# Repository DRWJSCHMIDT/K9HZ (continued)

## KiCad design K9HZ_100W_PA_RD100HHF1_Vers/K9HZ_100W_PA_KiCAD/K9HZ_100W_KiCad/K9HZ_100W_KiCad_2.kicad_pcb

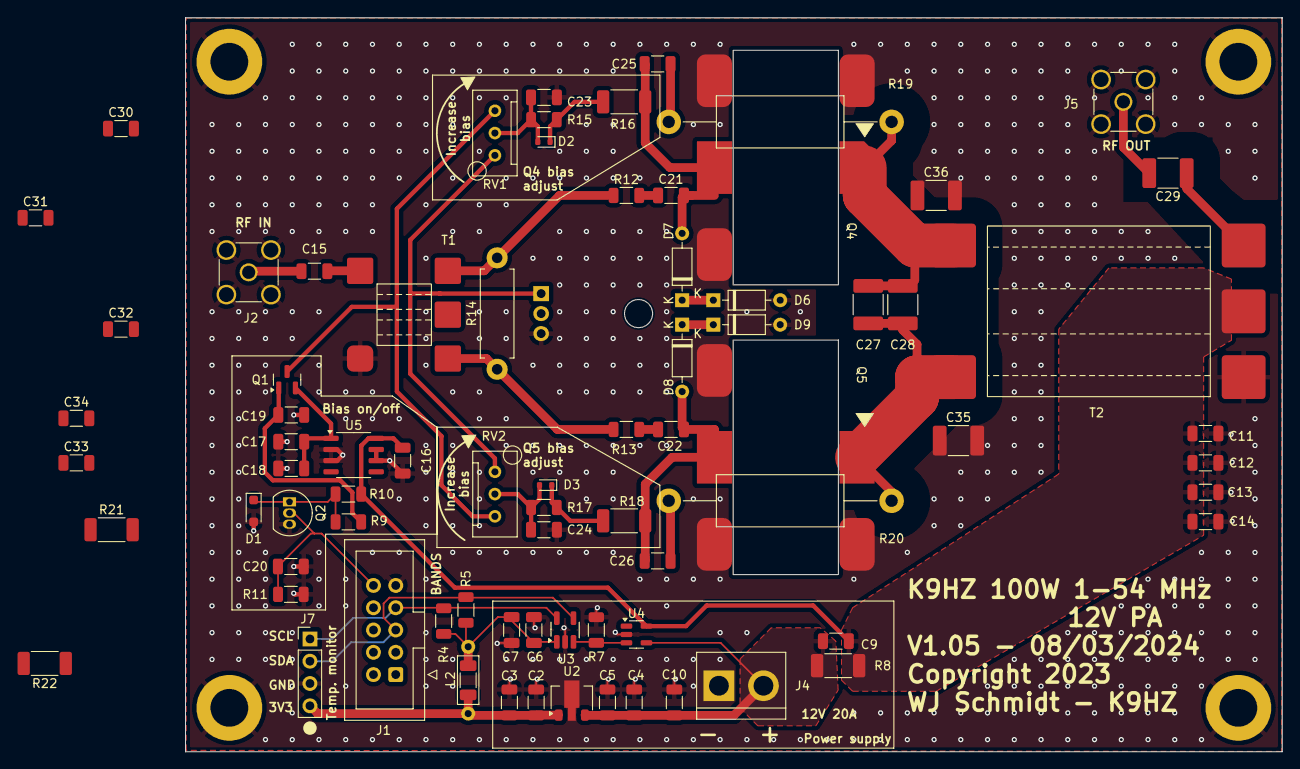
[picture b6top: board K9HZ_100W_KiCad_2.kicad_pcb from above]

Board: 2 copper layers, 125.0 x 83.7 mm, 83 parts (1 on the bottom side), 35 nets.

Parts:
C2, C4, C7, C9, C10, C15, C18, C20, C23, C24, C30, C31: 0.1uF 50V; C_1206_3216Metric
C3: 2.2uF 6V; C_1206_3216Metric
C5: 1uF 16V; C_1206_3216Metric
C6: 10uF 6V; C_1206_3216Metric
C11, C12, C13, C14: 0.1uF; C_1206_3216Metric
C16, C17: 1uF 50V; C_1206_3216Metric
C19, C21, C22: 0.01uF 50V; C_1206_3216Metric
C25, C26: 4.7nF 100V; C_1206_3216Metric
C27, C28: 470pF 500V; C_1812_4532Metric_Pad1.57x3.40mm_HandSolder
C29: 0.1uF 500V; C_1812_4532Metric_Pad1.57x3.40mm_HandSolder
C32, C33: 100 pF 50V; C_1206_3216Metric
C34: 200pF 50V; C_1206_3216Metric
C35, C36: 100pF 500V; C_1812_4532Metric_Pad1.57x3.40mm_HandSolder
D1: 7.1V 1W; D_SOD-323_HandSoldering
D2, D3: 1N4148; D_SOD-523
D6, D7, D8, D9: 3.6V; D_DO-35_SOD27_P7.62mm_Horizontal
H1, H2, H3, H4: MountingHole_4.3mm_M4_DIN965_Pad
J1: BANDS; IDC-Header_2x05_P2.54mm_Vertical
J2: RF_IN; SMA_Amphenol_901-144_Vertical
J4: 12V, 20A; TerminalBlock_bornier-2_P5.08mm
J5: RF_OUT; SMA_Amphenol_901-144_Vertical
J7: Temp monitor; PinHeader_1x04_P2.54mm_Vertical
L2: FB; L_Axial_L5.3mm_D2.2mm_P7.62mm_Horizontal_Vishay_IM-1
L3: FB; L_1206_3216Metric_Pad1.22x1.90mm_HandSolder
Q1: BSS84; SOT-23
Q2: BS170; TO-92_Inline
Q3: BD677; TO-126-3_Horizontal_TabUp
Q4: RD100HHF1C; RD100HHF1-suspended
Q5: RD100HHF1C; RD100HHF1-suspended-v2
R4, R5: 5k6; R_1206_3216Metric
R7: 3.0k 1%; R_1206_3216Metric
R8: 0.005 Ohm 4W; R_2010_5025Metric_Pad1.40x2.65mm_HandSolder
R9: 3k; R_1206_3216Metric
R10: 510R; R_1206_3216Metric
R11: 6k8; R_1206_3216Metric
R12, R13: 10R; R_1206_3216Metric
R14: 200R 2W; R_Axial_DIN0411_L9.9mm_D3.6mm_P12.70mm_Horizontal
R15, R17: 220R; R_1206_3216Metric
R16, R18: 1k; R_2010_5025Metric_Pad1.40x2.65mm_HandSolder
R19, R20: 150R 3W; R_Axial_DIN0614_L14.3mm_D5.7mm_P25.40mm_Horizontal
R21, R22: 2.2k; R_2010_5025Metric_Pad1.40x2.65mm_HandSolder
RV1, RV2: 2.2k; Potentiometer_Bourns_3296W_Vertical
T1: BN43-2402; Toroid_6Pin_BN-43-2402_7mm_6.2mm
T2: BN43-3312; Toroid_6Pin_BN-43-3312_19.5mm_25.4mm
U2: AP7381-33Y-13; SOT-89-3
U3: MCP3021A0T-E/OT; SOT-23-5_HandSoldering
U4: ZXCT1010; SOT-23-5
U5: L4931CDT50; SO-8_3.9x4.9mm_P1.27mm

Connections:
+3V3: C2.2, C3.2, J7.4, L2.1, L3.1, U2.1 (VO)
+12P: C9.2, C11.1, C12.1, C13.1, C14.1, C16.2, R8.1, R10.1, T2.4 (SC), U4.5 (Vs-), U5.8 (VI)
+12V: C4.2, C5.2, C9.1, C10.1, J4.2, R8.2, U2.3 (VI), U4.4 (Vs+)
/RXTX: C20.2, J1.10, Q2.2 (G), R11.2
/SCL: J1.7, J7.1, R4.2, U3.5 (SCL)
/SDA: J1.5, J7.2, R5.2, U3.4 (SDA)
GND: C2.1, C3.1, C4.1, C5.1, C6.1, C7.1, C10.2, C11.2, C12.2, C13.2, C14.2, C16.1, C17.1, C18.1, C19.1, C20.1, C23.2, C24.1, C32.1, C33.1, C35.2, C36.2, D1.2 (A), D6.2 (A), D9.2 (A), H1.1, H2.1, H3.1, H4.1, J1.9, J2.2 (Ext), J4.1, J5.2 (Ext), J7.3, Q2.3 (S), Q3.3 (E), Q4.2 (S), Q5.2 (S), R7.1, R11.1, T1.2 (AB), T2.1 (AA), U2.2 (GND), U3.2 (VSS), U4.2 (GND), U5.2 (GND), U5.3 (GND), U5.6 (GND), U5.7 (GND)
unnamed: C21.2, C30.2, R12.1
unnamed: C22.2, C31.2, R13.1
unnamed: C25.1, R19.2
unnamed: C26.1, R20.2
unnamed: D1.1 (K), Q2.1 (D), R9.1, R10.2
unnamed: C23.1, D2.2 (A), R15.1, RV1.2
unnamed: D2.1 (K), R15.2, R16.1
unnamed: C24.2, D3.2 (A), R17.1, RV2.2
unnamed: D3.1 (K), R17.2, R18.1
unnamed: D6.1 (K), D7.1 (K)
unnamed: C25.2, D7.2 (A), Q4.3 (G), R12.2, R13.2, R16.2, R21.2
unnamed: C26.2, D8.2 (A), Q5.3 (G), R18.2, R22.1
unnamed: D8.1 (K), D9.1 (K)
unnamed: C15.1, J2.1 (In)
unnamed: C29.2, J5.1 (In)
unnamed: Q1.3 (D), RV1.3, RV2.3
unnamed: C19.2, Q1.1 (G), R9.2
unnamed: C17.2, C18.2, Q1.2 (S), U5.1 (VO)
unnamed: Q3.1 (B), RV1.1, RV2.1
unnamed: C27.1, C28.1, C36.1, Q4.1 (D), R19.1, T2.3 (SA)
unnamed: C27.2, C28.2, C35.1, Q5.1 (D), R20.1, T2.5 (SB)
unnamed: R21.1, R22.2
unnamed: C15.2, T1.1 (AA)
unnamed: C22.1, C31.1, C32.2, C34.1, R14.1, T1.3 (SA)
unnamed: C21.1, C30.1, C33.2, C34.2, R14.2, T1.5 (SB)
unnamed: C29.1, T2.2 (AB)
unnamed: R7.2, U3.3 (AIN), U4.3 (OUT)
unnamed: C6.2, C7.2, L2.2, L3.2, R4.1, R5.1, U3.1 (VDD)

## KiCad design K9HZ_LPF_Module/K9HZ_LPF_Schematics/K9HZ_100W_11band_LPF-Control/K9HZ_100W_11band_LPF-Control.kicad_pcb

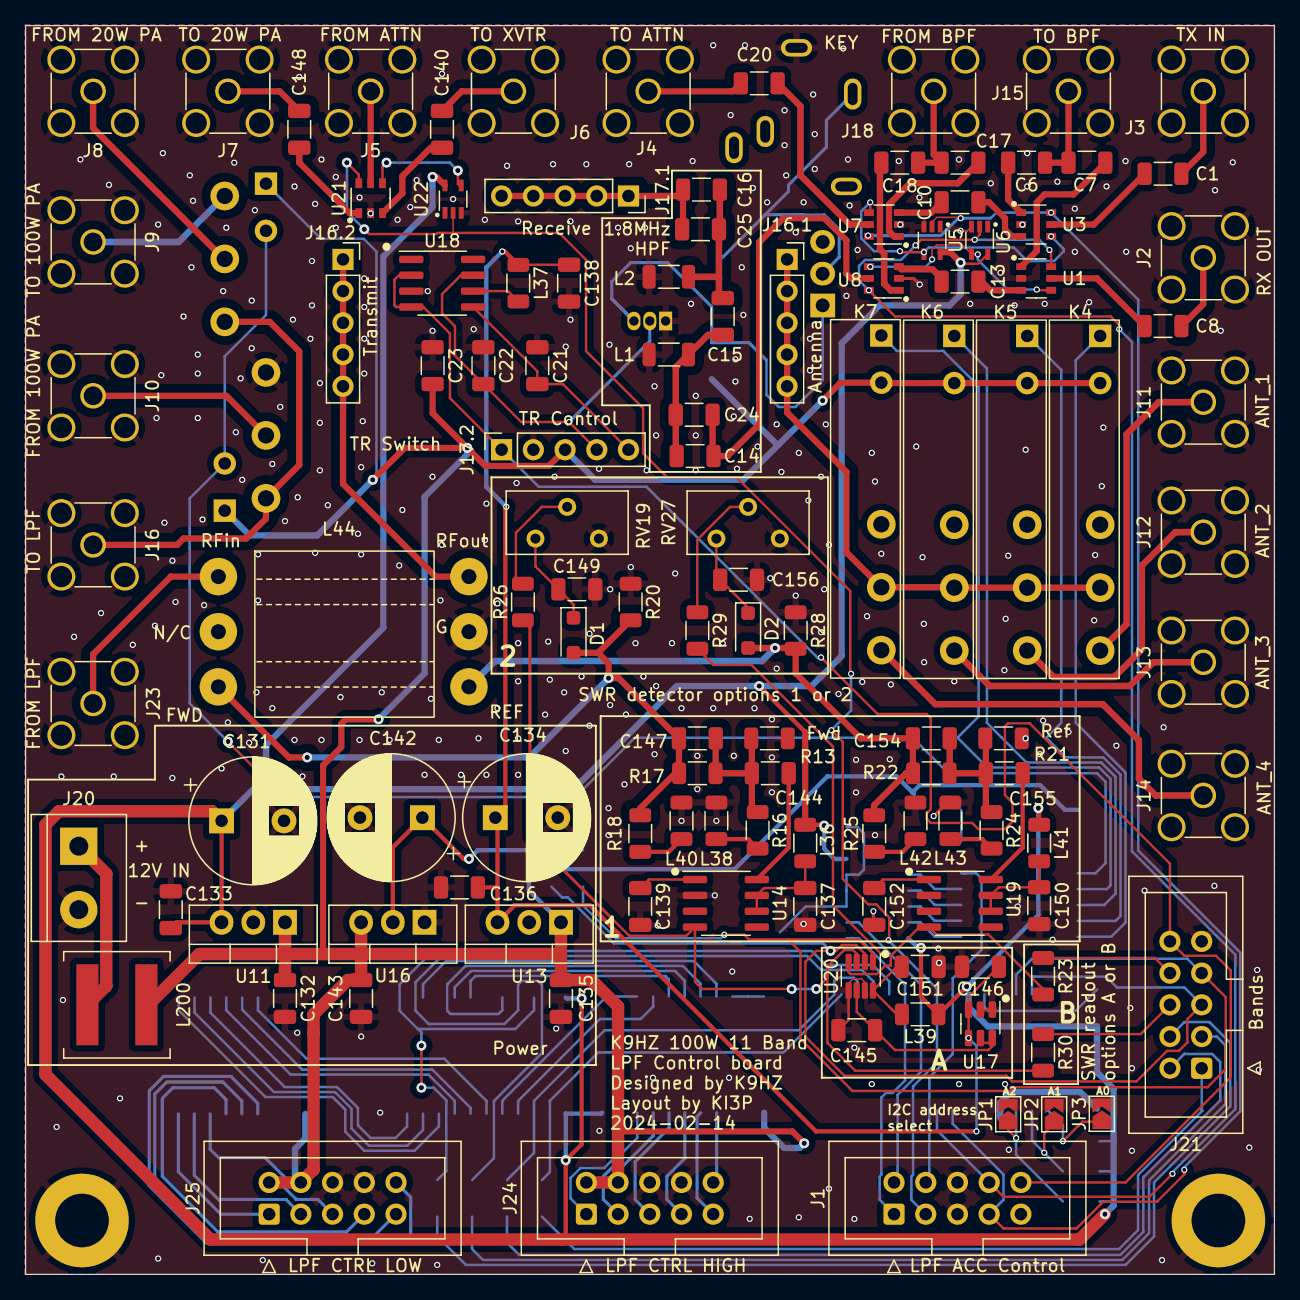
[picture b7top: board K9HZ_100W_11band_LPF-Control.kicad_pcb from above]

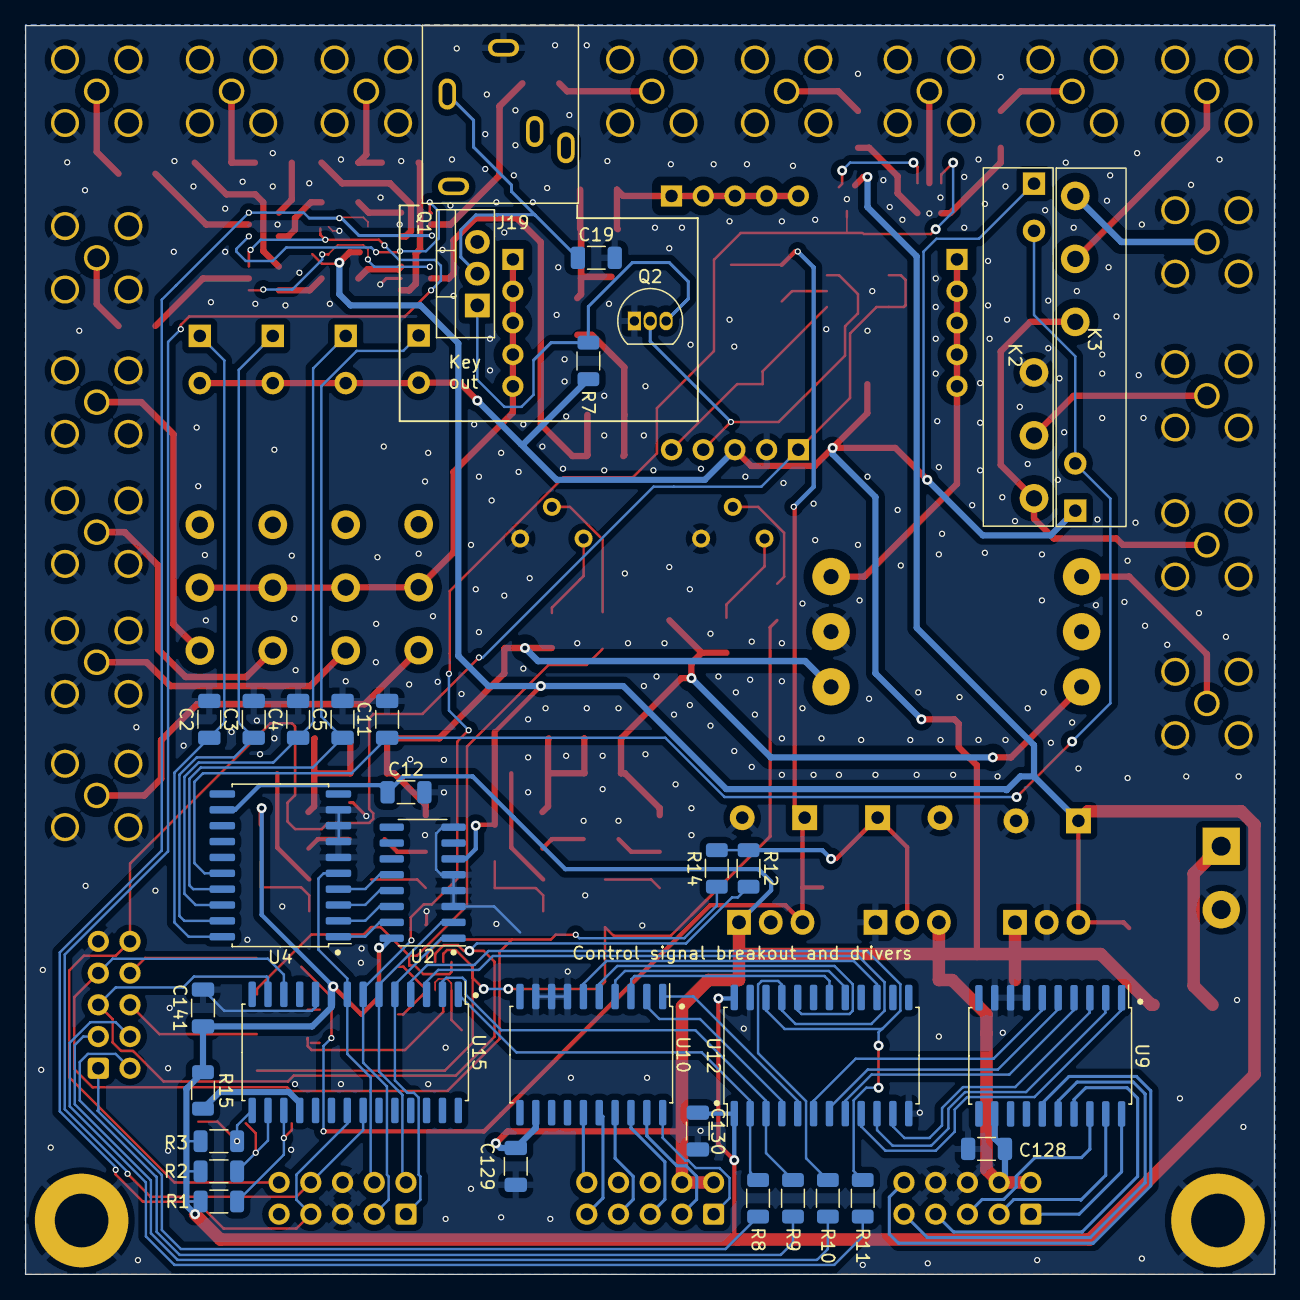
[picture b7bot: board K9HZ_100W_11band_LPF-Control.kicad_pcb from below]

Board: 4 copper layers, 100.0 x 100.0 mm, 155 parts (33 on the bottom side), 128 nets.

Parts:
C1, C2, C3, C4, C5, C6, C7, C8, C10, C11, C12, C13, C17, C18, C20, C21, C22, C23, C128, C129, C130, C137, C138, C139, C140, C141, C148, C150, C151, C152: 0.1uF 50V; C_1206_3216Metric
C14, C16: 1800pF 50V; C_1206_3216Metric
C15: 1000pF 50V; C_1206_3216Metric
C19: 15nF 50V; C_1206_3216Metric
C24, C25: 100pF 50V; C_1206_3216Metric
C131, C134: 220uF 16V; CP_Radial_D10.0mm_P5.00mm
C132, C133, C135, C136, C146: 1uF 50V; C_1206_3216Metric
C142: 100uF 6V; CP_Radial_D10.0mm_P5.00mm
C143, C145: 10uF 50V; C_1206_3216Metric
C144, C149, C155, C156: 10nF 50V; C_1206_3216Metric
C147, C154: 10pF 50V; C_1206_3216Metric
D1, D2: BAS70H,115; D_SOD-123F
H1, H2: MountingHole_4.3mm_M4_DIN965_Pad
J1: LPF ACC Control; IDC-Header_2x05_P2.54mm_Vertical
J2: TO_RECEIVER; SMA_Amphenol_901-144_Vertical
J3: FROM TX; SMA_Amphenol_901-144_Vertical
J4: TO ATTN; SMA_Amphenol_901-144_Vertical
J5: FROM ATTN; SMA_Amphenol_901-144_Vertical
J6: TO XVTR; SMA_Amphenol_901-144_Vertical
J7: TO 20W PA; SMA_Amphenol_901-144_Vertical
J8: FROM 20W PA; SMA_Amphenol_901-144_Vertical
J9: TO 100W PA; SMA_Amphenol_901-144_Vertical
J10: FROM 100W PA; SMA_Amphenol_901-144_Vertical
J11: ANT-1; SMA_Amphenol_901-144_Vertical
J12: ANT-2; SMA_Amphenol_901-144_Vertical
J13: ANT-3; SMA_Amphenol_901-144_Vertical
J14: ANT-4; SMA_Amphenol_901-144_Vertical
J15: TO BPF; SMA_Amphenol_901-144_Vertical
J16: TO LPF; SMA_Amphenol_901-144_Vertical
J16.1: ANTENNA; PinSocket_1x05_P2.54mm_Vertical
J16.2: TRANSMIT; PinSocket_1x05_P2.54mm_Vertical
J17.1: RECEIVE; PinSocket_1x05_P2.54mm_Vertical
J17.2: TR CTL; PinSocket_1x05_P2.54mm_Vertical
J18: FROM BPF; SMA_Amphenol_901-144_Vertical
J19: KEY OUT; Jack_3.5mm_STX-3081_Horizontal
J20: 12-13.8V; TerminalBlock_bornier-2_P5.08mm
J21: Bands; IDC-Header_2x05_P2.54mm_Vertical
J23: FROM LPF; SMA_Amphenol_901-144_Vertical
J24: LPF CTRL HI; IDC-Header_2x05_P2.54mm_Vertical
J25: LPF CTRL LOW; IDC-Header_2x05_P2.54mm_Vertical
JP1, JP2, JP3: SolderJumper_2_Open; SolderJumper-2_P1.3mm_Open_TrianglePad1.0x1.5mm
K2, K3, K4, K5, K6, K7: HF41F/12-ZS; Relay_SPDT_HF41F12-ZS
L1, L2: 3.3uH; L_1206_3216Metric
L36, L37, L39, L41: FB; R_1206_3216Metric
L38, L40, L42, L43: 22nH; R_1206_3216Metric
L44: 6_pin_transformer; Toroid_6Pin_BinocularCore_13.3mm_14.35mm
L200: 10uH 20%; L_Coilcraft_XAL7020-102
Q1: IRF630; TO-220-3_Vertical
Q2: 2N7000; TO-92_Inline
R1, R2, R3, R12, R14, R15: 2k2; R_1206_3216Metric
R7, R26, R29: 10k; R_1206_3216Metric
R8, R9, R10, R11, R23, R30: 0; R_1206_3216Metric
R13, R20, R21, R28: 52R3; R_1206_3216Metric
R16, R17, R18, R22, R24, R25: R_1206_3216Metric
RV19, RV27: 22k; Potentiometer_Bourns_3296Y_Vertical
U1, U3, U7, U8, U21: MASWSS0179; MASWSS0179-SOT-26
U2: 74HC237; SOIC-16_3.9x9.9mm_P1.27mm
U4, U9, U10: ULN2803C; SOIC-20W_7.5x12.8mm_P1.27mm
U5, U6, U22: SN74LVC1G04DCK; SOT-SC70
U11: LM7805CT; TO-220-3_Vertical
U12: CD74HC4514M96; SOIC-24W_7.5x15.4mm_P1.27mm
U13: L7808; TO-220-3_Vertical
U14, U19: AD8307; SOIC-8_3.9x4.9mm_P1.27mm
U15: MCP23017_SO; SOIC-28W_7.5x17.9mm_P1.27mm
U16: LM1117T-3.3; TO-220-3_Vertical
U17: REF3440IDBVR; SOT-23-6
U18: TC4428; SOIC-8_3.9x4.9mm_P1.27mm
U20: AD7991YRJZ; SOT-23-8

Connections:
+3V3: C142.1, R12.2, R14.2, U16.2 (VO)
+5V: C130.1, C131.1, C133.1, C141.1, L36.2, L39.2, L41.2, R1.2, R2.2, R3.2, R15.1, U2.6 (E2), U2.16 (VCC), U5.5 (VCC), U6.5 (VCC), U11.3 (VO), U12.1 (~LE), U12.24 (VCC), U15.9 (VDD), U22.5 (VCC)
+8V: C134.1, C136.1, C138.1, C146.2, L37.1, U13.3 (OUT), U17.3 (ENABLE), U17.4 (VIN)
+12V: C12.1, C23.2, C128.1, C129.1, C132.1, C135.1, C143.1, J17.2.3, J24.2, J24.4, J25.2, J25.4, K2.A1, K3.A1, K4.A2, K5.A2, K6.A2, K7.A2, L200.2, R7.1, U4.12 (COM), U9.12 (COM), U10.12 (COM), U11.1 (VI), U13.1 (IN), U16.3 (VI)
/6M: J24.9, U10.16 (O5)
/8R ~TX: C22.2, J17.2.4, Q2.2 (G), U18.7 (~OUT_A)
/8T TX: C21.2, J17.2.5, U18.5 (OUT_B)
/10M: J24.7, U10.17 (O4)
/12M: J24.5, U10.18 (O3)
/15M: J24.3, U10.19 (O2)
/17M: J24.1, U10.20 (O1)
/20M: J25.10, U9.15 (O6)
/30M: J25.9, U9.16 (O5)
/40M: J25.7, U9.17 (O4)
/60M: J25.5, U9.18 (O3)
/80M: J25.3, U9.19 (O2)
/100W_PA_SEL: C11.1, K2.A2, K3.A2, U4.16 (O5)
/160M: J25.1, U9.20 (O1)
/ANT1_SEL: C2.1, K4.A1, U4.20 (O1)
/ANT2_SEL: C3.1, K5.A1, U4.19 (O2)
/ANT3_SEL: C4.1, K6.A1, U4.18 (O3)
/ANT4_SEL: C5.1, K7.A1, U4.17 (O4)
/BIT0: J21.1, R8.2
/BIT1: J21.2, R9.2
/BIT2: J21.3, R10.2
/BIT3: J21.4, R11.2
/FWD: R26.1, R30.2, U14.4 (OUT), U20.3 (Vin0)
/FWD_V: J21.6, R30.1
/LPF_TO_SWR: J23.1 (In), L44.1
/NF: J24.10, U10.15 (O6)
/REF: R23.2, R29.2, U19.4 (OUT), U20.4 (Vin1)
/REF_V: J21.8, R23.1
/RF1: C1.2, J3.1 (In)
/RF7: C20.1, J4.1 (In)
/RF17: C140.2, J6.1 (In)
/RF18: C148.1, J7.1 (In)
/RF19: J8.1 (In), K2.11
/RF20: J9.1 (In), K2.14
/RF21: J16.1 (In), K2.12, K3.14
/RF22: J10.1 (In), K3.11
/RF23: J16.1.1, J16.1.2, J16.1.3, J16.1.4, J16.1.5, K4.11, K5.11, K6.11, K7.11
/RF24: J11.1 (In), K4.14
/RF27: J14.1 (In), K7.14
/RF28: C16.2, C25.2, J17.1.1, J17.1.2, J17.1.3, J17.1.4, J17.1.5
/RF29: C15.2, C16.1, C25.1, L2.1
/RF30: C14.2, C15.1, C24.2, L1.1
/RF34: C8.2, J2.1 (In)
/RF35: C147.2, D1.2 (A), L44.3, R17.1, R18.2, R20.2
/RF36: C154.2, D2.2 (A), L44.4, R22.1, R25.2, R28.2
/RF37: C154.1, C155.2, R21.2, R22.2, R24.2
/RF38: C144.2, C147.1, R13.2, R16.2, R17.2
/RRF2: C1.1, U3.5 (RFC)
/RRF3: C6.1, U3.1 (RF1)
/RRF4: C10.2, U3.3 (RF2)
/RRF5: C10.1, U7.3 (RF2)
/RRF6: C20.2, U7.5 (RFC)
/RRF8: C6.2, C7.1, J15.1 (In)
/RRF9: C17.2, C18.1, J18.1 (In)
/RRF10: C17.1, U7.1 (RF1)
/RRF11: C7.2, U1.1 (RF1)
/RRF12: C13.2, U8.3 (RF2)
/RRF13: C18.2, U8.1 (RF1)
/RRF14: J5.1 (In), U21.5 (RFC)
/RRF15: C140.1, U21.3 (RF2)
/RRF16: C148.2, U21.1 (RF1)
/RRF25: J12.1 (In), K5.14
/RRF26: J13.1 (In), K6.14
/RRF31: C14.1, C24.1, U8.5 (RFC)
/RRF32: C13.1, U1.3 (RF2)
/RRF33: C8.1, U1.5 (RFC)
/RX_BPF_SEL: J1.8, U1.6 (V1), U6.2, U8.6 (V1), U15.22 (GPA1)
/SCL: J21.7, R14.1, U15.12 (SCK), U20.1 (SCL)
/SDA: J21.5, R12.1, U15.13 (SDA), U20.2 (SDA)
/SWR_TO_PIN_DIODE_TR: J16.2.1, J16.2.2, J16.2.3, J16.2.4, J16.2.5, L44.2
/TX: J1.10, J17.2.1, J21.10, U18.2 (IN_A), U18.4 (IN_B)
/TX_BPF_SEL: J1.7, U3.6 (V1), U5.2, U7.6 (V1), U15.21 (GPA0)
/XVTR_SEL: J1.3, U15.7 (GPB6), U21.6 (V1), U22.2
GND: C2.2, C3.2, C4.2, C5.2, C11.2, C12.2, C19.2, C21.1, C22.1, C23.1, C128.2, C129.2, C130.2, C131.2, C132.2, C133.2, C134.2, C135.2, C136.2, C137.2, C138.2, C139.2, C141.2, C142.2, C143.2, C145.2, C146.1, C149.2, C150.2, C151.2, C152.2, C156.2, H1.1, H2.1, J1.5, J1.6, J2.2 (Ext), J3.2 (Ext), J4.2 (Ext), J5.2 (Ext), J6.2 (Ext), J7.2 (Ext), J8.2 (Ext), J9.2 (Ext), J10.2 (Ext), J11.2 (Ext), J12.2 (Ext), J13.2 (Ext), J14.2 (Ext), J15.2 (Ext), J16.2 (Ext), J17.2.2, J18.2 (Ext), J19.S, J20.2, J21.9, J23.2 (Ext), J24.6, J24.8, J25.6, J25.8, JP1.2 (B), JP2.2 (B), JP3.2 (B), K3.12, L1.2, L2.2, L38.2, L40.2, L42.2, L43.2, L44.5, Q1.3 (S), Q2.1 (S), R13.1, R20.1, R21.1, R28.1, RV19.3, RV27.3, U1.2 (GND), U2.3 (A2), U2.4 (~LE), U2.5 (~E1), U2.8 (GND), U3.2 (GND), U4.6 (I6), U4.7 (I7), U4.8 (I8), U4.9 (GND), U5.3 (GND), U6.3 (GND), U7.2 (GND), U8.2 (GND), U9.7 (I7), U9.8 (I8), U9.9 (GND), U10.7 (I7), U10.8 (I8), U10.9 (GND), U11.2 (GND), U12.12 (GND), U12.23 (~E), U13.2 (GND), U14.2 (COM), U15.10 (VSS), U16.1 (GND), U17.1 (GNDF), U17.2 (GNDS), U18.3 (GND), U19.2 (COM), U20.5 (Vin2), U20.7 (GND), U21.2 (GND), U22.3 (GND)
unnamed: C149.1, D1.1 (K), RV19.1
unnamed: C156.1, D2.1 (K), RV27.1
unnamed: J1.1, U2.1 (A0), U15.5 (GPB4)
unnamed: J1.2, U2.2 (A1), U15.6 (GPB5)
unnamed: J1.4, U4.5 (I5), U15.8 (GPB7)
unnamed: J20.1, L200.1
unnamed: JP1.1 (A), R1.1, U15.17 (A2)
unnamed: JP2.1 (A), R2.1, U15.16 (A1)
unnamed: JP3.1 (A), R3.1, U15.15 (A0)
unnamed: L38.1, R16.1
unnamed: L40.1, R18.1
unnamed: L42.1, R25.1
unnamed: L43.1, R24.1
unnamed: C19.1, J19.T, Q1.2 (D)
unnamed: Q1.1 (G), Q2.3 (D), R7.2
unnamed: R26.2, RV19.2
unnamed: R29.1, RV27.2
unnamed: U1.4 (V2), U6.4, U8.4 (V2)
unnamed: U2.15 (Y0), U4.1 (I1)
unnamed: U2.14 (Y1), U4.2 (I2)
unnamed: U2.13 (Y2), U4.3 (I3)
unnamed: U2.12 (Y3), U4.4 (I4)
unnamed: U3.4 (V2), U5.4, U7.4 (V2)
unnamed: U10.1 (I1), U12.5 (Y6)
unnamed: U10.2 (I2), U12.4 (Y7)
unnamed: U10.3 (I3), U12.18 (Y8)
unnamed: U10.4 (I4), U12.17 (Y9)
unnamed: U10.5 (I5), U12.20 (Y10)
unnamed: U10.6 (I6), U12.15 (Y15)
unnamed: R8.1, U12.2 (A0), U15.1 (GPB0)
unnamed: R9.1, U12.3 (A1), U15.2 (GPB1)
unnamed: R10.1, U12.21 (A2), U15.3 (GPB2)
unnamed: R11.1, U12.22 (A3), U15.4 (GPB3)
unnamed: U9.3 (I3), U12.11 (Y0)
unnamed: U9.1 (I1), U12.9 (Y1)
unnamed: U9.2 (I2), U12.10 (Y2)
unnamed: U9.4 (I4), U12.8 (Y3)
unnamed: U9.5 (I5), U12.7 (Y4)
unnamed: U9.6 (I6), U12.6 (Y5)
unnamed: C137.1, L36.1, U14.6 (ENB), U14.7 (VPS)
unnamed: C139.1, U14.1 (INM)
unnamed: C144.1, U14.8 (INP)
unnamed: R15.2, U15.18 (~RESET)
unnamed: C145.1, U17.6 (OUT_F), U20.6 (Vin3/Vref)
unnamed: L37.2, U18.6 (VDD)
unnamed: C150.1, L41.1, U19.6 (ENB), U19.7 (VPS)
unnamed: C152.1, U19.1 (INM)
unnamed: C155.1, U19.8 (INP)
unnamed: C151.1, L39.1, U20.8 (Vdd)
unnamed: U21.4 (V2), U22.4

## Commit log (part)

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2024-11-05 Github Restructure
    Github Restructure
2024-11-28 Updates
    Updates
2024-12-14 Update
    Update
2025-01-11 File Updates
    File Updates
2025-01-16 Update Amp Driver FIles
    Update Amp Driver FIles
2025-01-22 Update 3D Printer Files
    Update 3D Printer Files
2025-01-27 Simplified GITHUB Structure
    Simplified GITHUB Structure
2025-02-10 Rearrange GITHUB
    Rearrange GITHUB
2025-04-10 Update Files
    Update Files
2025-06-19 Fixed missing connection between pins 5 and 6 on U17, REF3440
2025-07-02 Update LPF Docs
    Update LPF Docs
2025-07-14 Update Tuner Files
    Update Tuner Files
2025-08-28 Rename LPF Files
    Rename LPF Files
2025-08-28 Updates for new PDF files
    Updates for new PDF Files
2025-09-07 Improve File structure
    Improve File Structure
2025-12-01 Added HDMI shield
    Added HDMI shield
2026-01-03 Add Switcher Project
    Added Switcher Project
2026-01-07 ATU Update
    ATU Update
2026-01-20 Updates for Tuner
    Updates for Tuner
2026-01-22 Tuner Updates
    Tuner Updates
2026-01-28 Update AT
    Update AT
2026-01-29 Tuner Update
    Tuner Update
2026-02-15 Update Assembly Instructions
    Update Assembly Instructions
2026-02-23 Update Tuner
    Update Tuner for Production
2026-02-27 Update Data
    Update Data
2026-03-17 Antenna Tuner Update
    Antenna Tuner Update
2026-04-07 Update projects
    Update projects
2026-04-08 Update Tuner
    Update Tuner
2026-05-07 Update Assembly Manuals
    Update Assembly Manuals
